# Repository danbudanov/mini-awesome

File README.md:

# Mini Awesome
A software defined ELF/VLF receiver, imlementing functionality of Stanford's AWESOME receiver on an SoC.

## Directory Structure
- **fpga** - SystemVerilog HDL modules and Quartus project files for implementing the
FPGA system on the SoC
- **software** - Contains the entirety of the software running on the SoC, including 
*fpga abstraction libraries*, *linux setup scripts*, and the Mini Awesome *application*
- **hardware** - EAGLE board files and component libraries for PCBs used in the design
- **resources** - useful resources and links for project

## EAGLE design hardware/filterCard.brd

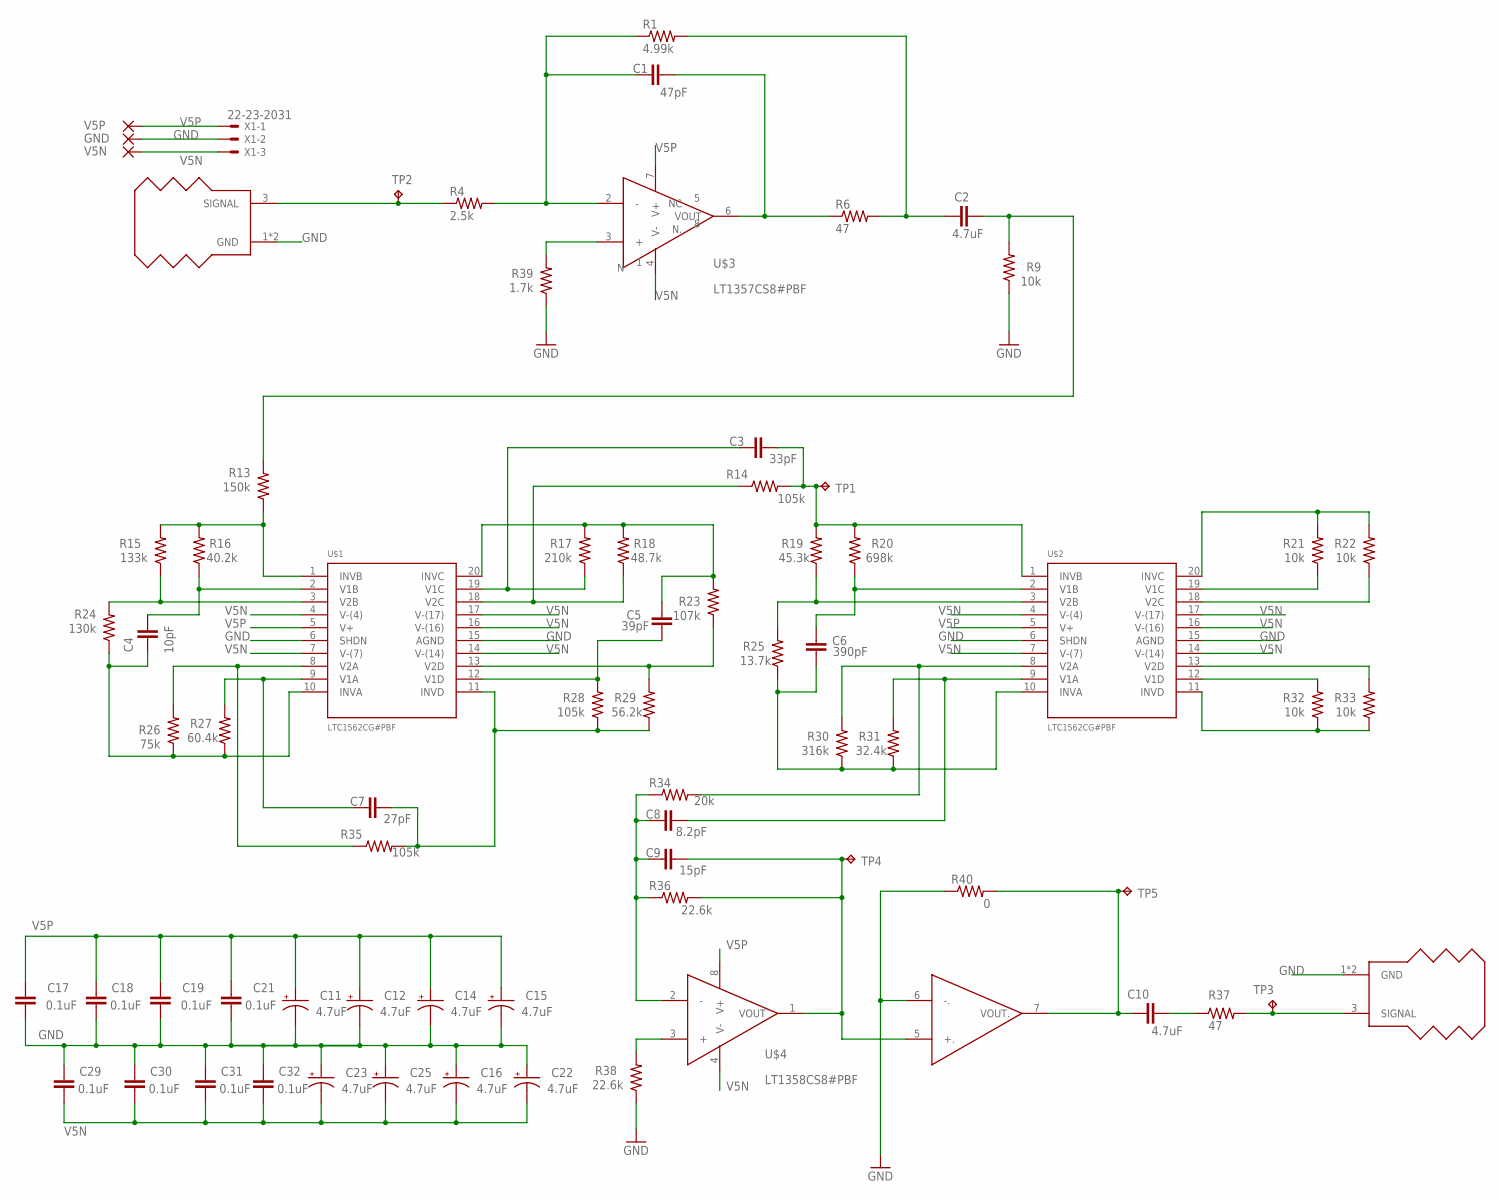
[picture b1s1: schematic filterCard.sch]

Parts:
C1: 47pF; 0603
C2, C10: 4.7uF; 1206
C3: 33pF; 1206
C4: 10pF; 1206
C5: 39pF; 1206
C6: 390pF; 1206
C7: 27pF; 1206
C8: 8.2pF; 1206
C9: 15pF; 1206
C11, C12, C14, C15, C16, C22, C23, C25: 4.7uF; 1206-POLAR
C17, C18, C19, C21, C29, C30, C31, C32: 0.1uF; 0603
GND: ground; 2,54/0,8
R1: 4.99k; R0603
R4: 2.5k; R0603
R6, R37: 47; R1206
R9, R21, R22, R32, R33: 10k; R1206
R13: 150k; R1206
R14, R28, R35: 105k; R1206
R15: 133k; R1206
R16: 40.2k; R1206
R17: 210k; R1206
R18: 48.7k; R1206
R19: 45.3k; R1206
R20: 698k; R1206
R23: 107k; R1206
R24: 130k; R1206
R25: 13.7k; R1206
R26: 75k; R1206
R27: 60.4k; R1206
R29: 56.2k; R1206
R30: 316k; R1206
R31: 32.4k; R1206
R34: 20k; R1206
R36, R38: 22.6k; R1206
R39: 1.7k; R0603
R40: 0; R0805
TP1, TP4, TP5: TPPAD1-17; P1-17
TP2, TP3: TPPAD1-13; P1-13
U$1, U$2: LTC1562CG#PBF; TSSOP20
U$3: LT1357CS8#PBF; 8-SOIC
U$4: LT1358CS8#PBF; 8-SOIC
U$5, U$6: MY_SMASMD; MY_SMA
V5N: -5; 2,54/0,8
V5P: 5; 2,54/0,8
X1: 22-23-2031

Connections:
GND: C11.-, C12.-, C14.-, C15.-, C16.+, C17.2, C18.2, C19.2, C21.2, C22.+, C23.+, C25.+, C29.1, C30.1, C31.1, C32.1, GND.1, R9.1, R38.1, R39.1, R40.1, U$1.6 (SHDN), U$1.15 (AGND), U$2.6 (SHDN), U$2.15 (AGND), U$4.6 (-.), U$5.1 (GND), U$5.2 (GND), U$6.1 (GND), U$6.2 (GND), X1.2
unnamed: C7.1, R27.2, U$1.9 (V1A)
unnamed: R26.2, R35.1, U$1.8 (V2A)
unnamed: C4.2, R24.1, R26.1, R27.1, U$1.10 (INVA)
unnamed: R15.1, R24.2, U$1.3 (V2B)
unnamed: C7.2, R28.1, R29.1, R35.2, U$1.11 (INVD)
unnamed: C4.1, R16.1, U$1.2 (V1B)
unnamed: R39.2, U$3.3 (+)
unnamed: C5.2, R28.2, U$1.12 (V1D)
unnamed: R13.1, R15.2, R16.2, U$1.1 (INVB)
unnamed: R23.1, R29.2, U$1.13 (V2D)
unnamed: C1.1, R1.1, R4.2, U$3.2 (-)
unnamed: C3.2, R14.2, R19.2, R20.2, TP1.TP, U$2.1 (INVB)
unnamed: C3.1, R17.1, U$1.19 (V1C)
unnamed: R14.1, R18.1, U$1.18 (V2C)
unnamed: C5.1, R17.2, R18.2, R23.2, U$1.20 (INVC)
unnamed: C10.1, R40.2, TP5.TP, U$4.7 (VOUT.)
unnamed: R19.1, R25.2, U$2.3 (V2B)
unnamed: C6.1, R20.1, U$2.2 (V1B)
unnamed: C1.2, R6.1, U$3.6 (VOUT)
unnamed: C6.2, R25.1, R30.1, R31.1, U$2.10 (INVA)
unnamed: C8.2, R31.2, U$2.9 (V1A)
unnamed: R30.2, R34.2, U$2.8 (V2A)
unnamed: C10.2, R37.1
unnamed: R21.1, U$2.19 (V1C)
unnamed: R22.1, U$2.18 (V2C)
unnamed: R21.2, R22.2, U$2.20 (INVC)
unnamed: R32.2, U$2.12 (V1D)
unnamed: R33.2, U$2.13 (V2D)
unnamed: R32.1, R33.1, U$2.11 (INVD)
unnamed: C2.1, R1.2, R6.2
unnamed: R4.1, TP2.TP, U$5.3 (SIGNAL)
unnamed: C2.2, R9.2, R13.2
unnamed: R37.2, TP3.TP, U$6.3 (SIGNAL)
unnamed: C8.1, C9.1, R34.1, R36.1, U$4.2 (-)
unnamed: R38.2, U$4.3 (+)
unnamed: C9.2, R36.2, TP4.TP, U$4.1 (VOUT), U$4.5 (+.)
V5N: C16.-, C22.-, C23.-, C25.-, C29.2, C30.2, C31.2, C32.2, U$1.4 (V-(4)), U$1.7 (V-(7)), U$1.14 (V-(14)), U$1.16 (V-(16)), U$1.17 (V-(17)), U$2.4 (V-(4)), U$2.7 (V-(7)), U$2.14 (V-(14)), U$2.16 (V-(16)), U$2.17 (V-(17)), U$3.4 (V-), U$4.4 (V-), V5N.1, X1.3
V5P: C11.+, C12.+, C14.+, C15.+, C17.1, C18.1, C19.1, C21.1, U$1.5 (V+), U$2.5 (V+), U$3.7 (V+), U$4.8 (V+), V5P.1, X1.1

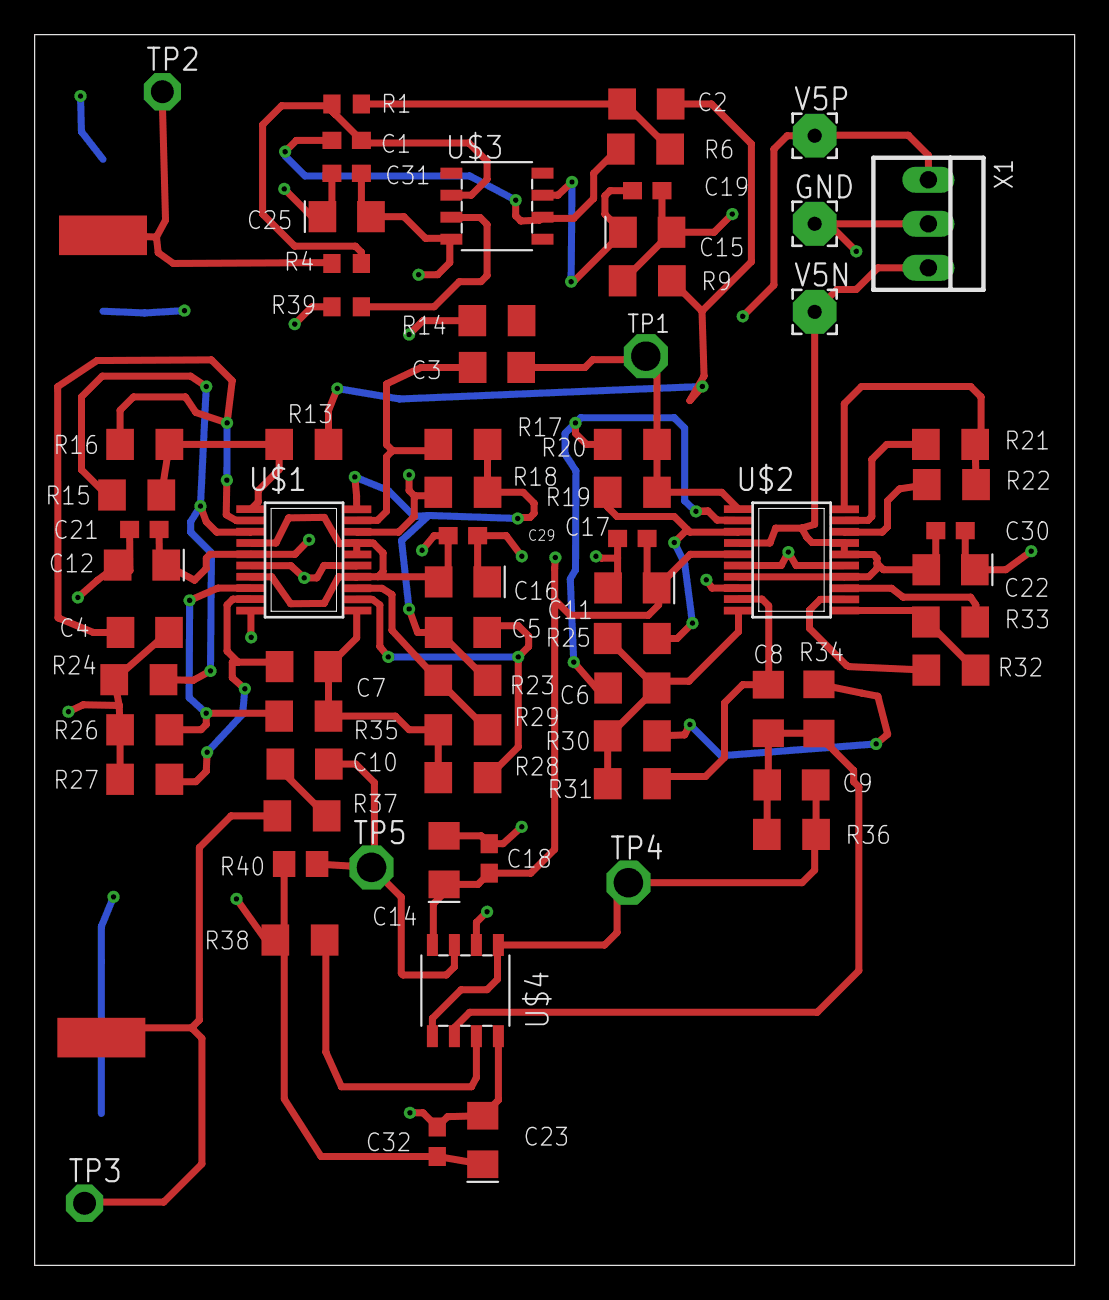
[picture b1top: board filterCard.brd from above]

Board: 4 copper layers, 60.0 x 71.0 mm, 73 parts (0 on the bottom side), 39 nets.

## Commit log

2017-09-03 laid out directory structure
2017-09-03 updated root readme
2017-09-03 brought in some sv work
2017-09-03 renamed to follow dir structure
2017-09-03 removed extra file
2017-09-03 quick format thing
2017-09-03 file location mistake
2017-09-04 started resources, added adc resources infos
2017-09-04 made resources md file be readme
2017-09-04 updated link
2017-09-04 added state counter
2017-09-05 the state machine for original is inherently messed up
2017-09-05 updated ADC module for proper fsm
2017-09-05 cleaned up old, bad file
2017-09-05 started verification phase
2017-09-05 minor_change
2017-09-05 ads now compiles
2017-09-05 updated resources with bullet to follow convention
2017-09-05 rmoved extran info
2017-09-05 Updated resources
2017-09-05 fixed bit ordering as data is clocked in
2017-09-07 began adc tb
2017-09-08 minor changes
2017-09-13 adc testbench/actual adc chip emulation
2017-09-13 changed file cases
2017-09-13 changed directory name convention
2017-09-13 some cleanup
2017-09-13 accidentally removed tb file
2017-09-13 did simulation, making some fixes
2017-09-13 some hdl and tb mods
2017-09-13 created fpga tb gitignore
2017-09-13 testbench fixes
2017-09-13 really close; clocking in is just one bit off
2017-09-17 modelsim changes
2017-09-19 switched to next state logic
2017-09-25 current simulation modules; need more elaborate verification
2017-09-25 added clock divider with 10 fold resolution of f_clk
2017-09-25 small clk div update
2017-09-26 continuing work on precise verification; otherwise, should be ready to hw test module
2017-09-26 added validation module for soc
2017-09-26 put in hardware validation test w AVMM
2017-09-26 slight restructure
2017-10-06 latest adc precise commit
2017-10-07 added quartus project; still need to do a few pin assignments, especially for ADC
2017-10-07 populated all soc instantiation fields
2017-10-07 small pin breakout fix
2017-10-07 small breakout fix; updated gitignore
2017-10-17 added in reset IP to testbench
2017-10-17 compiled tesbed
2017-10-23 added header generation script compatible with bash on windows
2017-10-24 cleanup extraneous swinfo file
2017-10-24 began adc testbed software
2017-10-31 began Quartus project and started QSys.
2017-10-31 modified (stripped out) top-level module
2017-11-07 generated memory path
2017-11-07 developing spoofer test modules
2017-11-07 finished spoofer avst state machine, now need to compile and test
2017-11-28 just in case
2017-11-28 nios msgdma prototypes
2017-12-05 wip msgdma descriptor configuration; a reference is included
2017-12-05 added test proj
2017-12-05 added testbench
2017-12-11 quick cleanup
2018-01-24 GIT test with Nick
2018-01-26 Removed print stmts, added timing b/w writes
2018-01-26 Optimized timing by removing some mutexes
2018-01-26 Removed all memMutex references. Cleaned up code.
2018-02-02 Added file I/O and Ctrl+C catcher code
2018-02-16 started serial, logger, and timestamp code
2018-03-07 First-draft SyncDAQwithGPS func from python code
